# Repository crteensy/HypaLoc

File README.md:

# HypaLoc
A tiny GNSS/magnetometer combo

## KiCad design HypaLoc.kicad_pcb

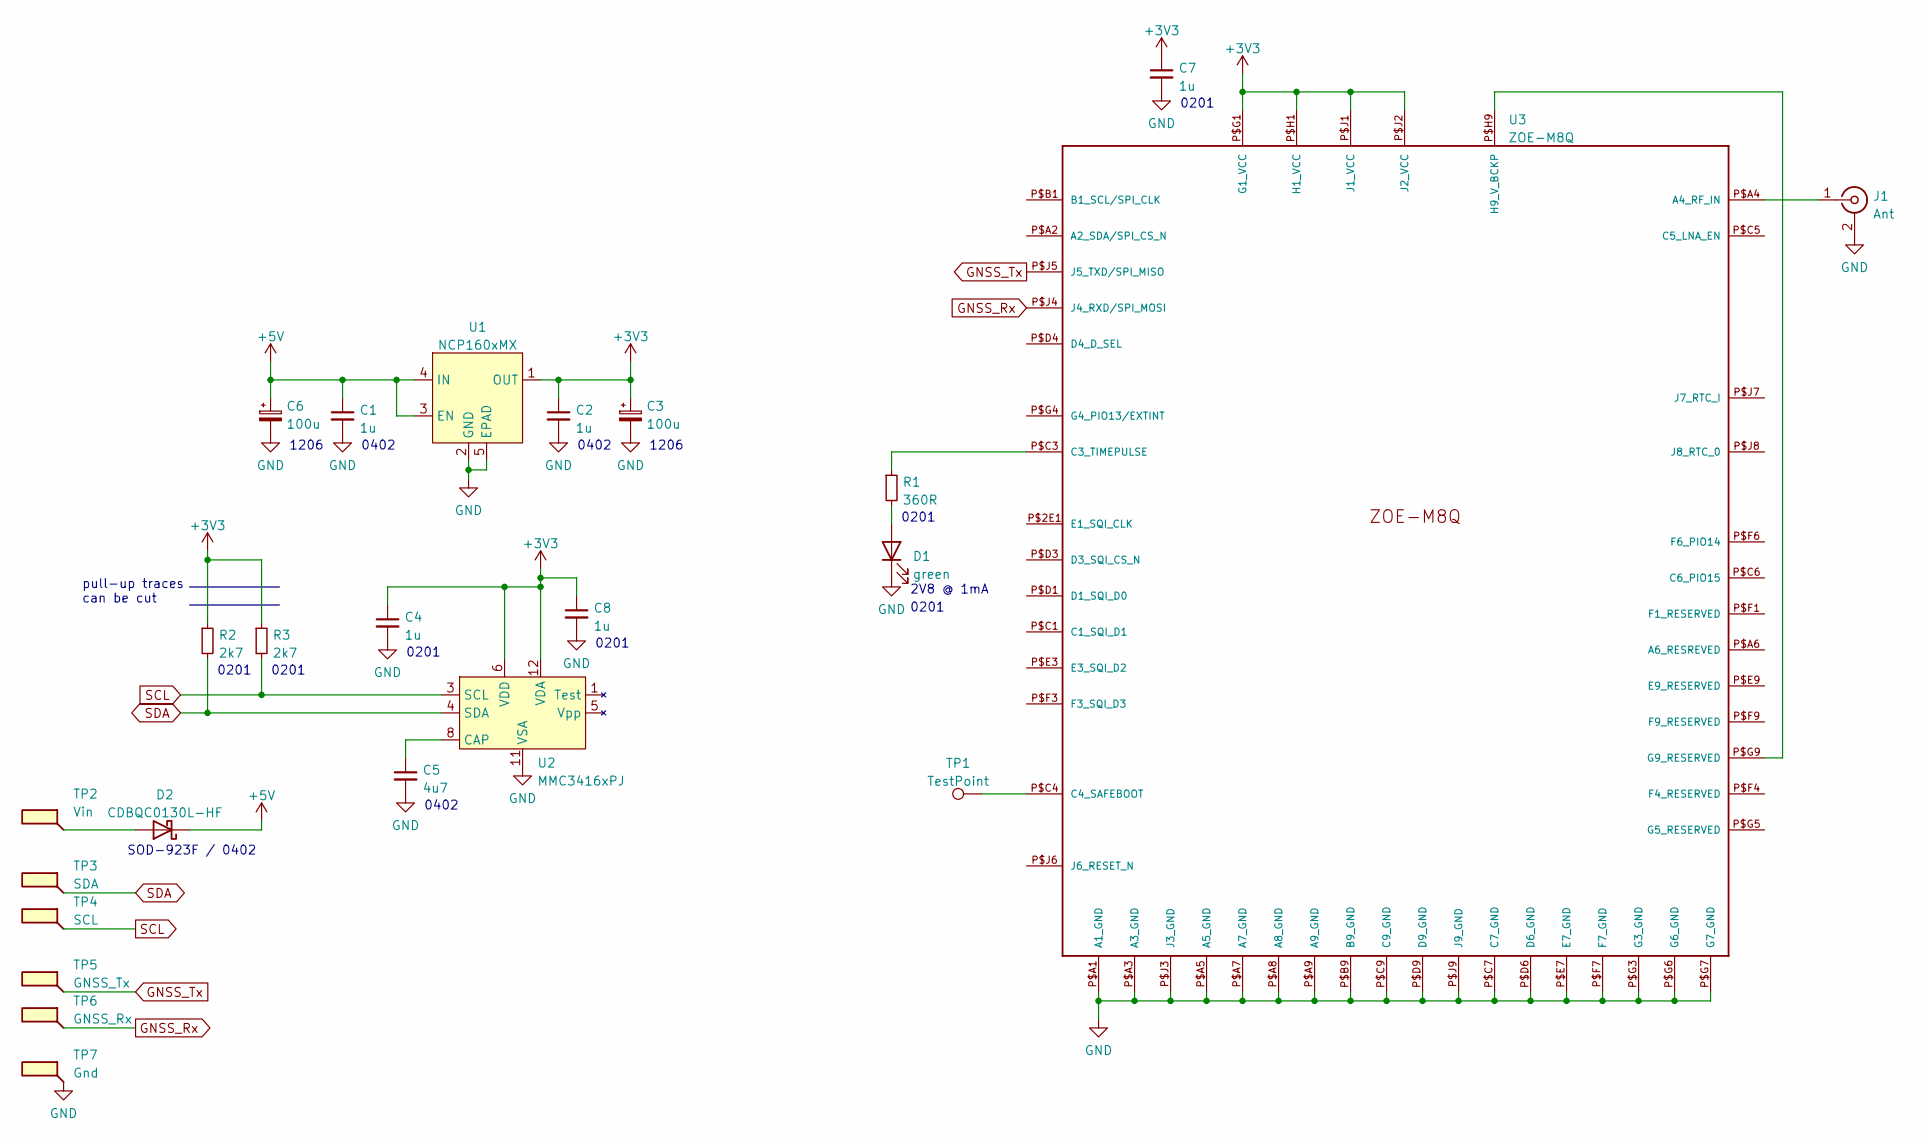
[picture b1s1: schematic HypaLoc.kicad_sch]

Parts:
C1, C2: 1u; C_0402_1005Metric
C3, C6: 100u; CP_EIA-3216-18_Kemet-A
C4, C7, C8: 1u; C_0201_0603Metric_mod
C5: 4u7; C_0402_1005Metric
D1: green; LED_0201_0603Metric
D2: CDBQC0130L-HF; D_SOD-932F_0402_1005Metric
J1: Ant; U.FL_Molex_MCRF_73412-0110_Vertical
R1: 360R; R_0201_0603Metric_mod
R2, R3: 2k7; R_0201_0603Metric_mod
TP1: TestPoint; TestPoint_Pad_D1.0mm
TP2: Vin; pad_1x1.5
TP3: SDA; pad_1x1.5
TP4: SCL; pad_1x1.5
TP5: GNSS_Tx; pad_1x1.5
TP6: GNSS_Rx; pad_1x1.5
TP7: Gnd; pad_1x1.5
U1: NCP160xMX; OnSemi-XDFN-4-1EP_1x1mm_P0.65mm_EP0.52x0.52mm
U2: MMC3416xPJ; BGA-12_4x4_1.6x1.6mm
U3: ZOE-M8Q; ZOE-M8

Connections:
+3V3: C2.1, C3.1, C4.1, C7.1, C8.1, R2.1, R3.1, U1.1 (OUT), U2.6 (VDD), U2.12 (VDA), U3.P$G1 (G1_VCC), U3.P$H1 (H1_VCC), U3.P$J1 (J1_VCC), U3.P$J2 (J2_VCC)
+5V: C1.1, C6.1, D2.1 (K), U1.3 (EN), U1.4 (IN)
GND: C1.2, C2.2, C3.2, C4.2, C5.2, C6.2, C7.2, C8.2, D1.1 (K), J1.2 (Ext), TP7.1, U1.2 (GND), U1.5 (EPAD), U2.11 (VSA), U3.P$A1 (A1_GND), U3.P$A3 (A3_GND), U3.P$A5 (A5_GND), U3.P$A7 (A7_GND), U3.P$A8 (A8_GND), U3.P$A9 (A9_GND), U3.P$B9 (B9_GND), U3.P$C7 (C7_GND), U3.P$C9 (C9_GND), U3.P$D6 (D6_GND), U3.P$D9 (D9_GND), U3.P$E7 (E7_GND), U3.P$F7 (F7_GND), U3.P$G3 (G3_GND), U3.P$G6 (G6_GND), U3.P$G7 (G7_GND), U3.P$J3 (J3_GND), U3.P$J9 (J9_GND)
GNSS_Rx: TP6.1, U3.P$J4 (J4_RXD/SPI_MOSI)
GNSS_Tx: TP5.1, U3.P$J5 (J5_TXD/SPI_MISO)
unnamed: C5.1, U2.8 (CAP)
unnamed: D1.2 (A), R1.2
unnamed: D2.2 (A), TP2.1
unnamed: J1.1 (In), U3.P$A4 (A4_RF_IN)
unnamed: R1.1, U3.P$C3 (C3_TIMEPULSE)
unnamed: TP1.1, U3.P$C4 (C4_SAFEBOOT)
unnamed: U3.P$G9 (G9_RESERVED), U3.P$H9 (H9_V_BCKP)
SCL: R3.2, TP4.1, U2.3 (SCL)
SDA: R2.2, TP3.1, U2.4 (SDA)

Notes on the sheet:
1206
0201
0402
SOD-923F / 0402
pull-up traces can be cut
2V8 @ 1mA

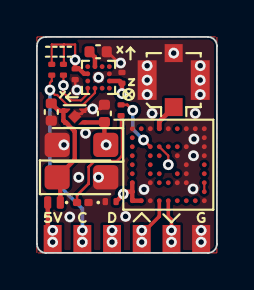
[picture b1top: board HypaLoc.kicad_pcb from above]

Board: 4 copper layers, 10.0 x 12.0 mm, 24 parts (1 on the bottom side), 14 nets.

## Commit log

2022-06-09 add schematic pdf
